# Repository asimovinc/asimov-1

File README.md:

# Asimov v1: Open-Source Humanoid Robot

Asimov is an open-source humanoid robot that you can build, train and customize.

<p align="center">
  <a href="https://asimov.inc">Website</a> ·
  <a href="https://manual.asimov.inc">Manual</a> ·
  <a href="https://asimov.inc/diy-kit">DIY Kit</a> ·
  <a href="https://static.asimov.inc/asimov/v1/asimov-v1-20260420.html">3D Model</a> ·
  <a href="https://discord.gg/HzDfGN7kUw">Discord</a> ·
  <a href="https://x.com/asimovinc">X</a> ·
  <a href="https://forum.menlo.ai">Forum</a>
</p>

Asimov v1 is a 1.2 m, 35 kg biped with 25 actuated degrees of freedom. This repository contains the mechanical CAD, electrical CAD, simulation model, and onboard software to build, simulate, and customize Asimov v1.

---

## Specifications

| Spec | Value |
|---|---|
| Height | 1.2 m |
| Weight | 35 kg |
| Degrees of Freedom | 25 actuated + 2 passive |
| Legs | 6 DOF x 2 + toe x 2 |
| Arms | 5 DOF x 2 (shoulder pitch/roll/yaw, elbow, wrist yaw) |
| Torso | 1 DOF waist yaw, 10 W 4 ohm speaker, 6 DOF IMU |
| Head | 2 DOF neck (neck yaw, neck pitch), Quad microphone array, 2MP monocular camera |
| CAN Bus | 5 @ 1Mbps + 1 @ 500kbps |
| Onboard Compute | Raspberry Pi 5 (media + network) + Radxa CM5 (motion control) |
| Structural Materials | 7075 aluminium, MJF PA12 nylon |

| Activity | Load |
|---|---|
| Squat | 5 kg |
| Bicep curl | 15 kg each arm |
| Lateral raise | 18 kg each arm |

---

## Build your own Asimov

> [!TIP]
> **Option 1: DIY Kit:** Everything you need to build Asimov v1, unassembled. $499 deposit to reserve. $15,000 target price. Ships summer 2026. [Pre-order →](https://asimov.inc/diy-kit)

> [!NOTE]
> **Option 2: Self-source:** Pull the [BOM](https://manual.asimov.inc/v1/bom) and fabricate everything yourself. [Assembly Manual →](https://manual.asimov.inc)

### DIY Kit

| Category | Included | Not Included |
|---|---|---|
| Hardware | All BOM components (unassembled), power supply & cabling, spare parts | Tools, hands |
| Compute | RPi edge board, motion control board, network board, power distribution board | 4G/5G modules |
| Sensors | Monocular camera, IMUs, mic, speaker, motor joint states | Lidar, 360 cam |
| Safety | Wireless E-Stop, safety guidelines | Battery |
| Docs | Quick start guide, manual, DIY build videos | — |

**[Pre-order the Asimov v1 DIY Kit →](https://asimov.inc/diy-kit)**

### Self-source

Start with the repo-local [fabrication manifest](mechanical/FABRICATION_MANIFEST.csv) for the CAD-derived part inventory, then cross-reference the [BOM](https://manual.asimov.inc/v1/bom) and assembly manual for procurement details, sourcing, and fabrication notes.

**[Assembly Manual →](https://manual.asimov.inc)**

---

## Fabrication manifest

The CAD-derived fabrication manifest can be checked locally:

```bash
python3 scripts/generate_fabrication_manifest.py --check
```

---

## Roadmap

| Status | Item |
|---|---|
| ✅ | Mechanical CAD — 7 subassemblies |
| ✅ | MuJoCo simulation model |
| ✅ | Electrical wiring harness |
| ✅ | Electrical schematics & PCB files |
| 🔜 | Asimov API |
| 🔜 | Locomotion policy |
| 🔜 | Mobile app |

---

## Work with us

- **Build questions?**: Ask in the [forum](https://forum.menlo.ai) or open a [GitHub Issue](https://github.com/asimovinc/asimov-v1/issues) for bugs and contributions.
- **Deploying Asimov?**: [Talk to us →](mailto:bd@menlo.ai)
- **Supply chain partner?**: If you manufacture actuators, structural components, or electronics and want to be part of the Asimov supply chain, reach out.
[bd@menlo.ai](mailto:bd@menlo.ai)

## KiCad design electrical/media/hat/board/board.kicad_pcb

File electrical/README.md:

## Motion Control Board

The Motion Control Board (MCB) is a carrier board designed for the Radxa CM5, providing comprehensive connectivity for robotic applications.

- The board serves as a carrier board for the Radxa CM5.
- Power is supplied via a 5V input through an XT30 connector.
- A UART TTL debug port is available for serial debugging purposes.
- The LSM6DSV IMU is located at the bottom of the board, with an I2C connector available if an external IMU is required.
- All signal connections use JST-GH connectors
- LCSC component IDs are attached in the KiCad source files for direct JLCPCB fabrication and assembly.

### Communication Ports

| Port Type | Quantity | Details |
|-----------|----------|---------|
| CAN (Native) | 3 | Direct CAN interfaces |
| CAN (SPI-CAN) | 3 | CAN via SPI bridge |
| USB 2.0 | 3 | USB interfaces |
| Ethernet | 1 | 1Gbps |
| RS485 | 2 | Serial communication |
| I2C | 1 | I2C interface |

### Port Mapping

| Port ID | Purpose |
|---------|---------|
| C0 | Left leg bus |
| C1 | Right leg bus |
| C2 | Right arm bus |
| C3 | Left arm bus |
| C4 | Waist-neck bus |
| C5 | BMS bus |

> The waist-neck bus requires a different cabling setup for this revision of the MCB: Waist -> Neck yaw -> Neck pitch -> MCB port C4

## Wiring

 was utilised for representing the wiring harness of the robot. 

Please refer to WireViz documentation for available visualisation options.
### Cable Naming Convention

```
W-<ID>-<TYPE>
ID = unique ID
TYPE = Power (PWR) or Signal (SIG) cable bundle
```

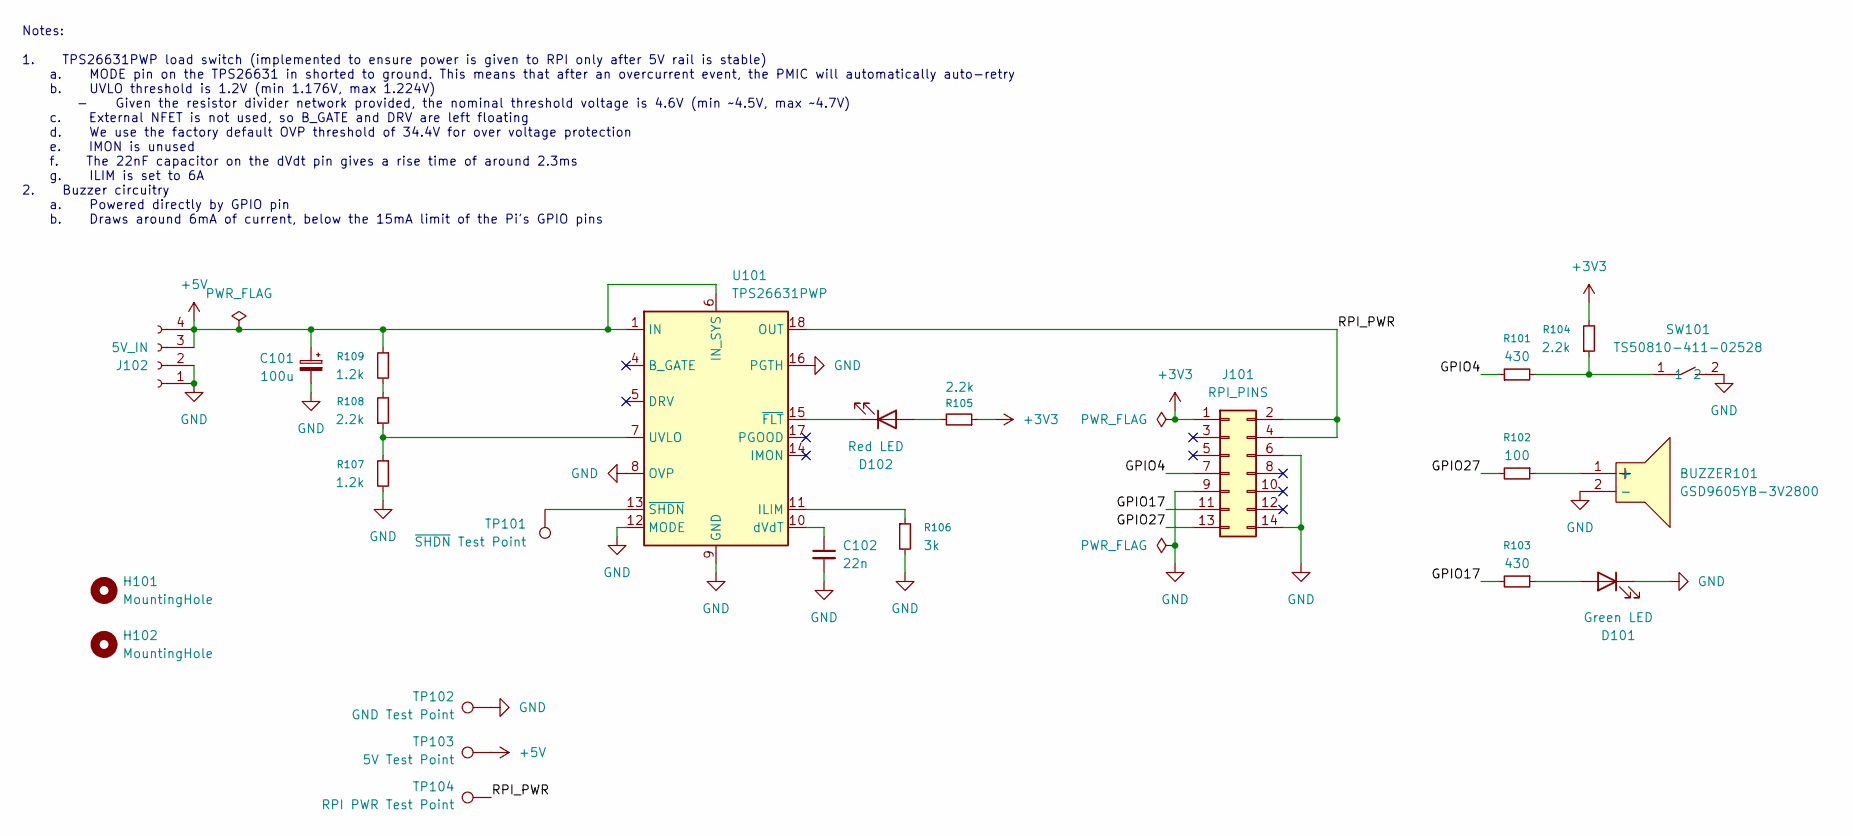
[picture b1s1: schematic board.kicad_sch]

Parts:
BUZZER101: GSD9605YB-3V2800; BUZ-SMD_GSD9605YB-3V2800; MPN GSD9605YB-3V2800; LCSC Part C255327
C101: 100u; CP_EIA-7343-31_Kemet-D; LCSC C600555
C102: 22n; C_0402_1005Metric; LCSC C1532
D101: Green LED; LED_0603_1608Metric; LCSC C965804
D102: Red LED; LED_0603_1608Metric; LCSC C2286
H101, H102: MountingHole; MountingHole_2.5mm
J101: RPI_PINS; PinSocket_2x07_P2.54mm_Vertical; LCSC C5116484
J102: 5V_IN; JST_XH_B4B-XH-A_1x04_P2.50mm_Vertical; LCSC C144395
R101, R103: 430; R_0402_1005Metric; LCSC C137868
R102: 100; R_0402_1005Metric; LCSC C25076
R104, R105, R108: 2.2k; R_0402_1005Metric; LCSC C25879
R106: 3k; R_0603_1608Metric; LCSC C4211
R107, R109: 1.2k; R_0402_1005Metric; LCSC C2909307
SW101: TS50810-411-02528; SW-SMD_L6.2-W3.7-LS8.0; MPN TS50810-411-02528; LCSC Part C42400876
TP101: ~{SHDN} Test Point; TestPoint_Keystone_5015_Micro_Mini; LCSC C5199798
TP102: GND Test Point; TestPoint_Keystone_5015_Micro_Mini; LCSC C5199798
TP103: 5V Test Point; TestPoint_Keystone_5015_Micro_Mini; LCSC C5199798
TP104: RPI PWR Test Point; TestPoint_Keystone_5015_Micro_Mini; LCSC C5199798
U101: TPS26631PWP; HTSSOP-20-1EP_4.4x6.5mm_P0.65mm_EP3.4x6.5mm_Mask2.96x2.96mm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; LCSC C2866319

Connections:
+3V3: J101.1, R104.2, R105.1
+5V: C101.1, J102.3, J102.4, R109.1, TP103.1 (1_1), U101.1 (IN), U101.2 (IN), U101.3 (IN), U101.6 (IN_SYS)
/GPIO4: J101.7, R101.1
/GPIO17: J101.11, R103.2
/GPIO27: J101.13, R102.2
/RPI_PWR: J101.2, J101.4, TP104.1 (1_1), U101.18 (OUT), U101.19 (OUT), U101.20 (OUT)
GND: BUZZER101.2 (-), C101.2, C102.2, D101.1 (K), J101.6, J101.9, J101.14, J102.1, J102.2, R106.2, R107.2, SW101.2, TP102.1 (1_1), U101.8 (OVP), U101.9 (GND), U101.12 (MODE), U101.16 (PGTH), U101.21 (GND)
unnamed: BUZZER101.1 (+), R102.1
unnamed: D101.2 (A), R103.1
unnamed: D102.2 (A), R105.2
unnamed: D102.1 (K), U101.15 (~FLT)
unnamed: R101.2, R104.1, SW101.1
unnamed: R108.2, R109.2
unnamed: R106.1, U101.11 (ILIM)
unnamed: R107.1, R108.1, U101.7 (UVLO)
unnamed: C102.1, U101.10 (dVdT)
unnamed: TP101.1 (1_1), U101.13 (~SHDN)

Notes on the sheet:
Notes: 1. TPS26631PWP load switch (implemented to ensure power is given to RPI only after 5V rail is stable) a. MODE pin on the TPS26631 in shorted to ground. This means that after an overcurrent event, the PMIC will automatically auto-retry b. UVLO threshold is 1.2V (min 1.176V, max 1.224V) - Give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

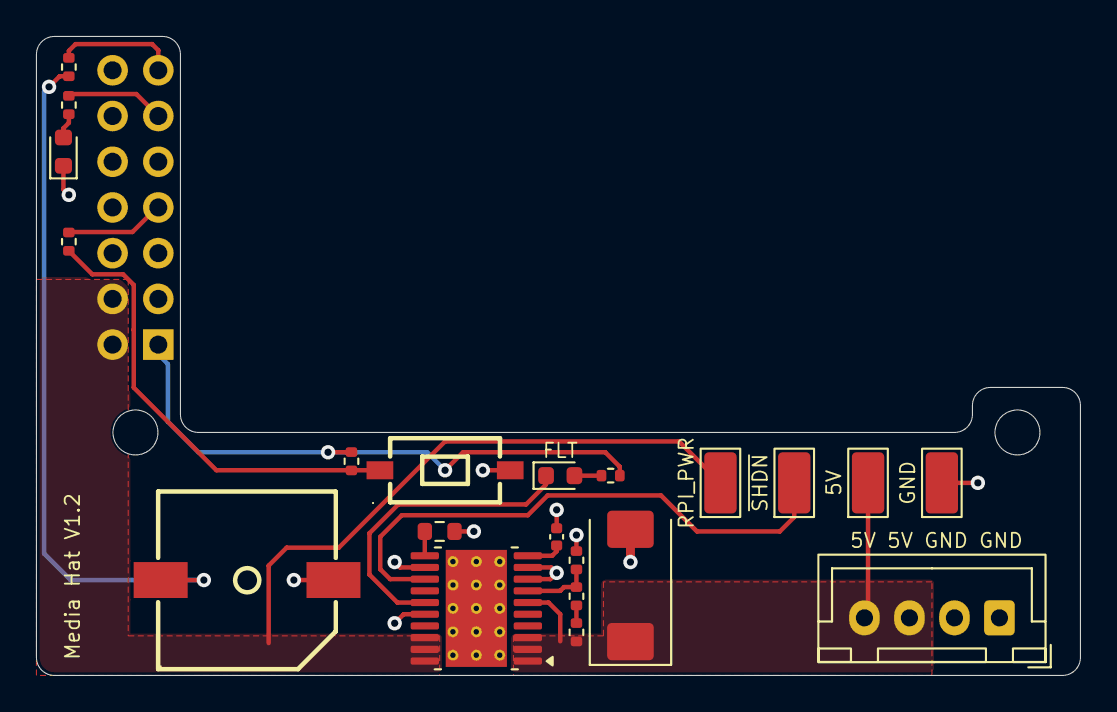
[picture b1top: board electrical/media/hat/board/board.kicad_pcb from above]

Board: 2 copper layers, 58.0 x 35.5 mm, 24 parts (1 on the bottom side), 17 nets.

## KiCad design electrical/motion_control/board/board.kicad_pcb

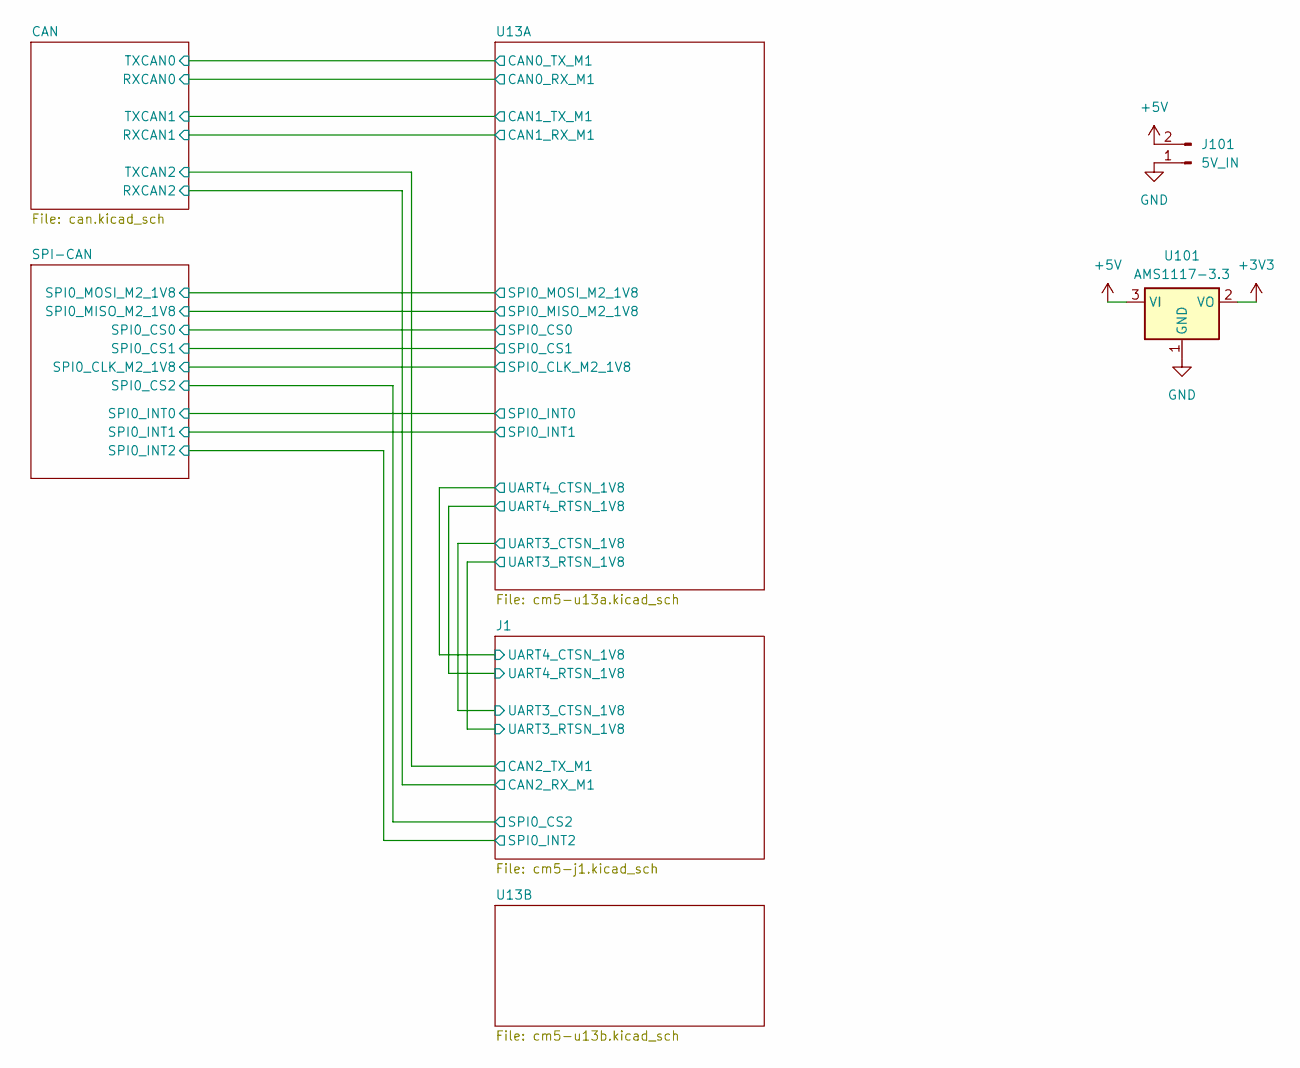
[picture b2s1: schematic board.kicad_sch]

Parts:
J101: 5V_IN; AMASS_XT30UPB-F_1x02_P5.0mm_Vertical; LCSC C108769
U101: AMS1117-3.3; SOT-223-3_TabPin2; LCSC C6186

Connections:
+3V3: U101.2 (VO); also elsewhere on the board
+5V: J101.2, U101.3 (VI); also elsewhere on the board
GND: J101.1, U101.1 (GND); also elsewhere on the board

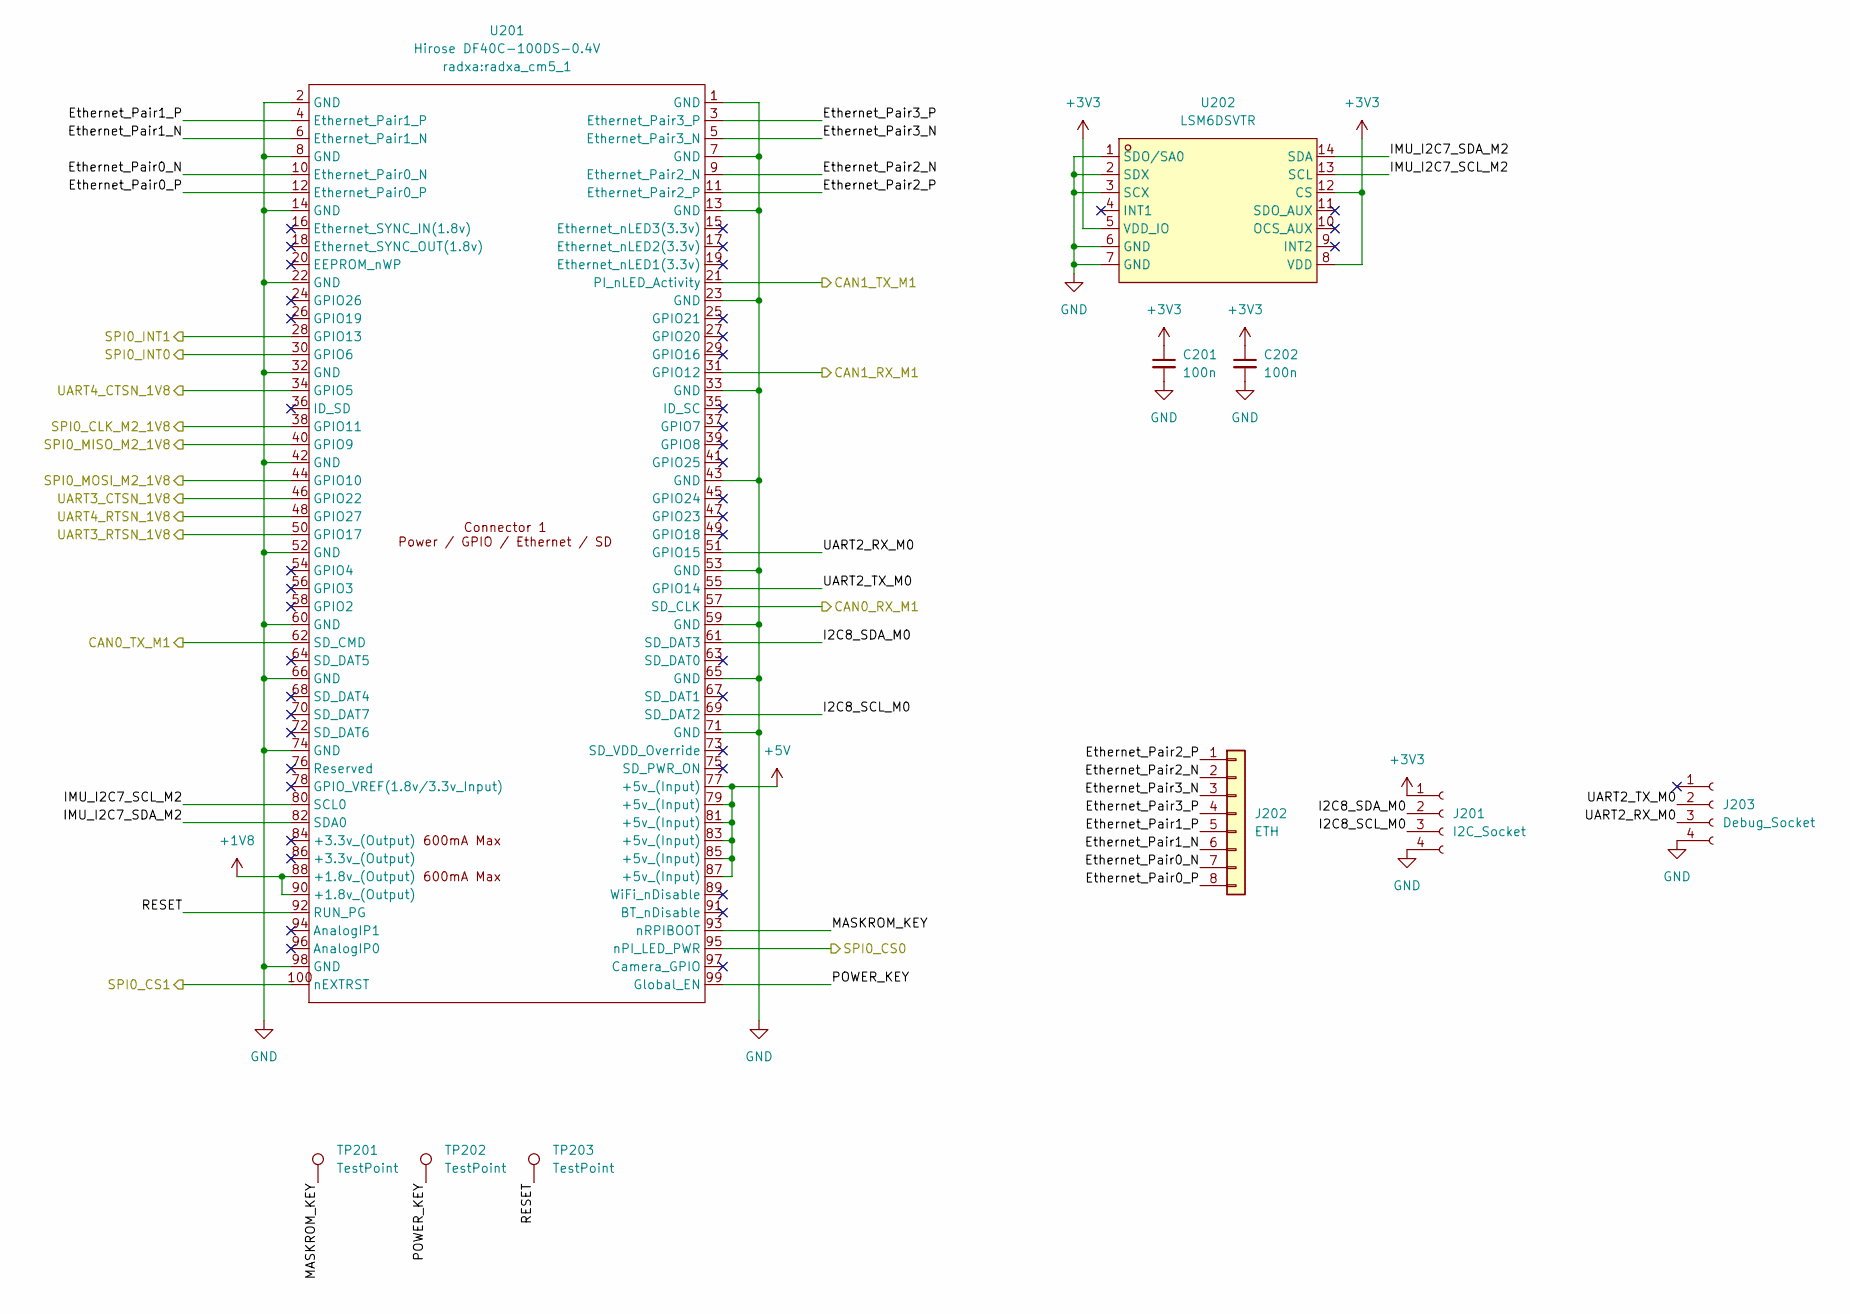
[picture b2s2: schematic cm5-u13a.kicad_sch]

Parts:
C201, C202: 100n; C_0402_1005Metric; LCSC C77020
J201: I2C_Socket; JST_GH_SM04B-GHS-TB_1x04-1MP_P1.25mm_Horizontal; LCSC C51940118
J202: ETH; JST_GH_BM08B-GHS-TBT_1x08-1MP_P1.25mm_Vertical; LCSC C133062
J203: Debug_Socket; JST_GH_SM04B-GHS-TB_1x04-1MP_P1.25mm_Horizontal; LCSC C51940118
TP201, TP202, TP203: TestPoint; TestPoint_Pad_D1.0mm
U201: Hirose DF40C-100DS-0.4V; radxa_cm5_1; LCSC C597931
U202: LSM6DSVTR; LGA-14_L3.0-W2.5-P0.50-TL; LCSC Part C5267399

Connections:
+1V8: U201.88 (+1.8v_(Output)), U201.90 (+1.8v_(Output)); also elsewhere on the board
+3V3: C201.1, C202.1, J201.1, U202.5 (VDD_IO), U202.8 (VDD), U202.12 (CS); also elsewhere on the board
+5V: U201.77 (+5v_(Input)), U201.79 (+5v_(Input)), U201.81 (+5v_(Input)), U201.83 (+5v_(Input)), U201.85 (+5v_(Input)), U201.87 (+5v_(Input)); also elsewhere on the board
/CAN/RXCAN0: U201.57 (SD_CLK); also elsewhere on the board
/CAN/RXCAN1: U201.31 (GPIO12); also elsewhere on the board
/CAN/TXCAN0: U201.62 (SD_CMD); also elsewhere on the board
/CAN/TXCAN1: U201.21 (PI_nLED_Activity); also elsewhere on the board
/J1/UART3_CTSN_1V8: U201.46 (GPIO22); also elsewhere on the board
/J1/UART3_RTSN_1V8: U201.50 (GPIO17); also elsewhere on the board
/J1/UART4_CTSN_1V8: U201.34 (GPIO5); also elsewhere on the board
/J1/UART4_RTSN_1V8: U201.48 (GPIO27); also elsewhere on the board
/SPI-CAN/SPI0_CLK_M2_1V8: U201.38 (GPIO11); also elsewhere on the board
/SPI-CAN/SPI0_CS0: U201.95 (nPI_LED_PWR); also elsewhere on the board
/SPI-CAN/SPI0_CS1: U201.100 (nEXTRST); also elsewhere on the board
/SPI-CAN/SPI0_INT0: U201.30 (GPIO6); also elsewhere on the board
/SPI-CAN/SPI0_INT1: U201.28 (GPIO13); also elsewhere on the board
/SPI-CAN/SPI0_MISO_M2_1V8: U201.40 (GPIO9); also elsewhere on the board
/SPI-CAN/SPI0_MOSI_M2_1V8: U201.44 (GPIO10); also elsewhere on the board
/U13A/Ethernet_Pair0_N: J202.7, U201.10 (Ethernet_Pair0_N)
/U13A/Ethernet_Pair0_P: J202.8, U201.12 (Ethernet_Pair0_P)
/U13A/Ethernet_Pair1_N: J202.6, U201.6 (Ethernet_Pair1_N)
/U13A/Ethernet_Pair1_P: J202.5, U201.4 (Ethernet_Pair1_P)
/U13A/Ethernet_Pair2_N: J202.2, U201.9 (Ethernet_Pair2_N)
/U13A/Ethernet_Pair2_P: J202.1, U201.11 (Ethernet_Pair2_P)
/U13A/Ethernet_Pair3_N: J202.3, U201.5 (Ethernet_Pair3_N)
/U13A/Ethernet_Pair3_P: J202.4, U201.3 (Ethernet_Pair3_P)
/U13A/I2C8_SCL_M0: J201.3, U201.69 (SD_DAT2)
/U13A/I2C8_SDA_M0: J201.2, U201.61 (SD_DAT3)
/U13A/IMU_I2C7_SCL_M2: U201.80 (SCL0), U202.13 (SCL)
/U13A/IMU_I2C7_SDA_M2: U201.82 (SDA0), U202.14 (SDA)
/U13A/MASKROM_KEY: TP201.1, U201.93 (nRPIBOOT)
/U13A/POWER_KEY: TP202.1, U201.99 (Global_EN)
/U13A/RESET: TP203.1, U201.92 (RUN_PG)
/U13A/UART2_RX_M0: J203.3, U201.51 (GPIO15)
/U13A/UART2_TX_M0: J203.2, U201.55 (GPIO14)
GND: C201.2, C202.2, J201.4, J203.4, U201.1 (GND), U201.2 (GND), U201.7 (GND), U201.8 (GND), U201.13 (GND), U201.14 (GND), U201.22 (GND), U201.23 (GND), U201.32 (GND), U201.33 (GND), U201.42 (GND), U201.43 (GND), U201.52 (GND), U201.53 (GND), U201.59 (GND), U201.60 (GND), U201.65 (GND), U201.66 (GND), U201.71 (GND), U201.74 (GND), U201.98 (GND), U202.1 (SDO/SA0), U202.2 (SDX), U202.3 (SCX), U202.6 (GND), U202.7 (GND); also elsewhere on the board

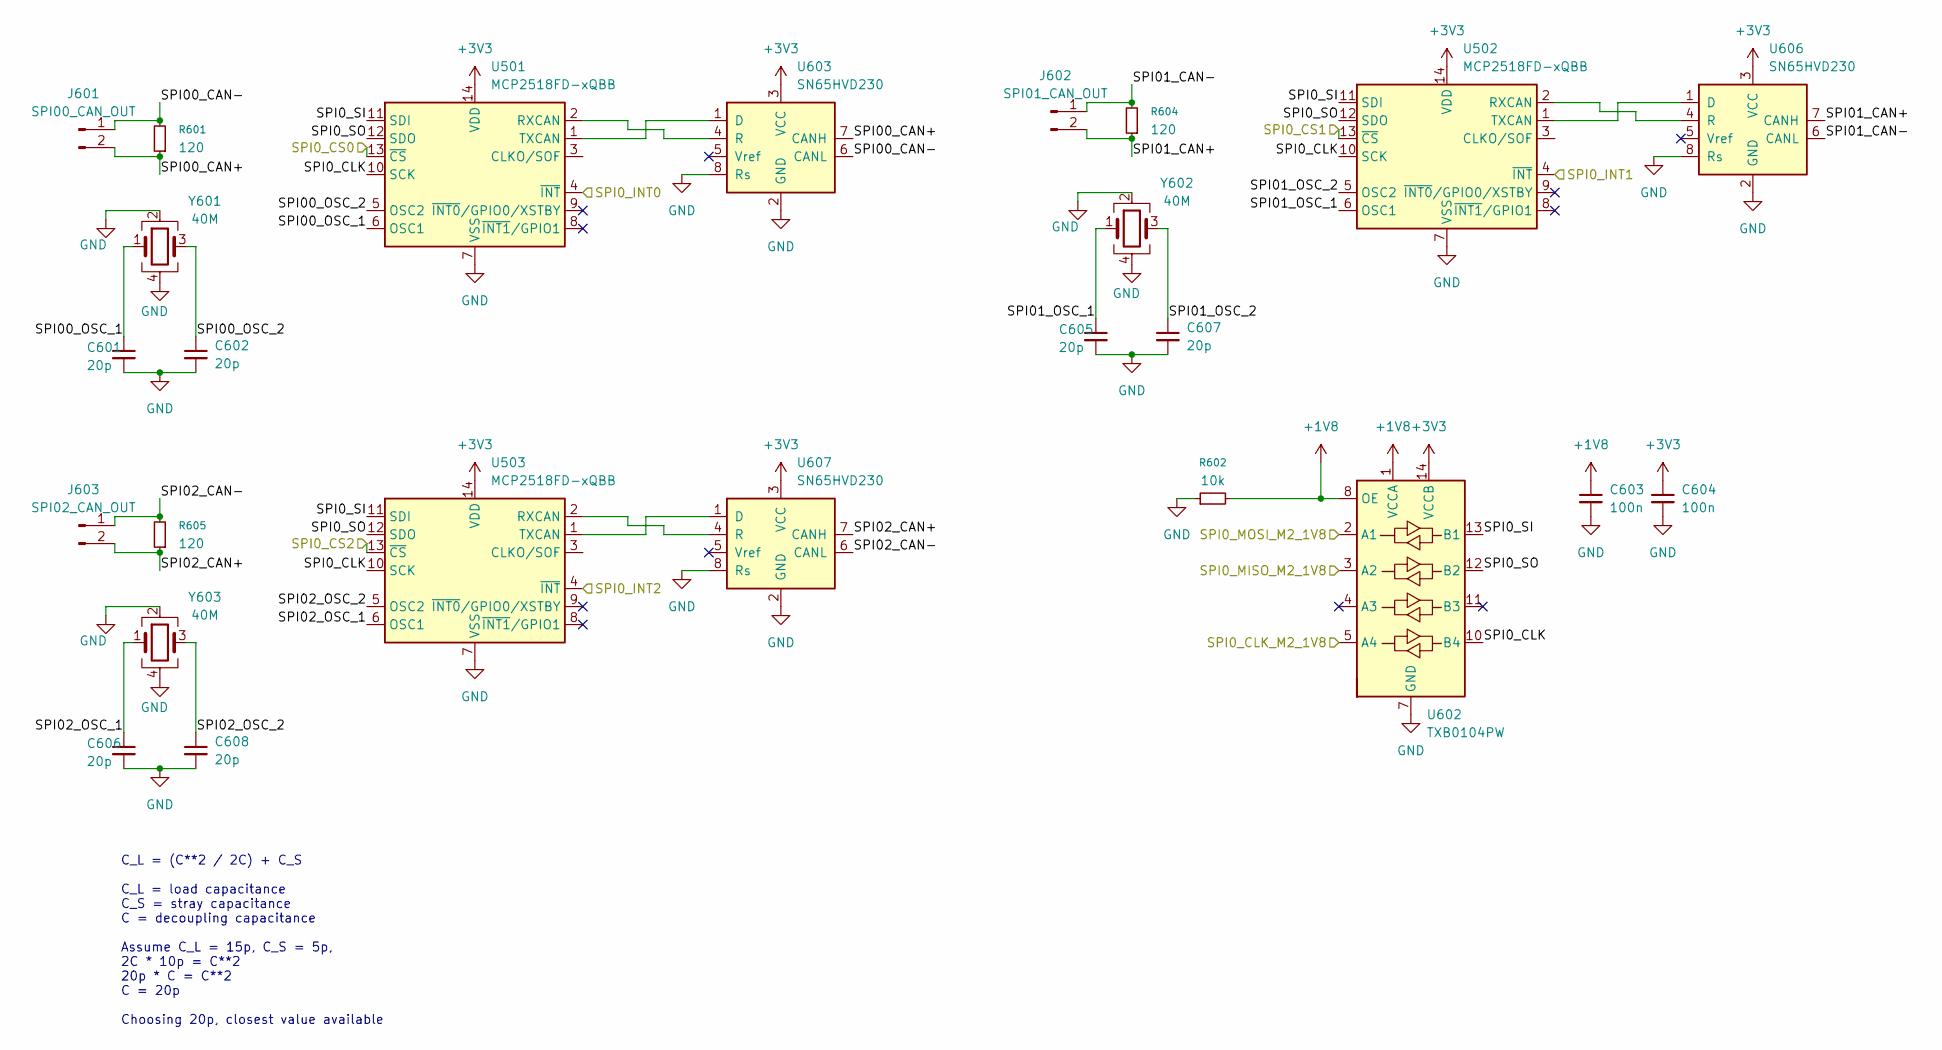
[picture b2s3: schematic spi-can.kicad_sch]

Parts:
C601, C602, C605, C606, C607, C608: 20p; C_0603_1608Metric; LCSC C165732
C603, C604: 100n; C_0402_1005Metric; LCSC C77020
J601: SPI00_CAN_OUT; JST_GH_SM02B-GHS-TB_1x02-1MP_P1.25mm_Horizontal; LCSC C189893
J602: SPI01_CAN_OUT; JST_GH_SM02B-GHS-TB_1x02-1MP_P1.25mm_Horizontal; LCSC C189893
J603: SPI02_CAN_OUT; JST_GH_SM02B-GHS-TB_1x02-1MP_P1.25mm_Horizontal; LCSC C189893
R601, R604, R605: 120; R_0402_1005Metric; LCSC C114758
R602: 10k; R_0402_1005Metric; LCSC C190095
U501, U502, U503: MCP2518FD-xQBB; SOIC-14_3.9x8.7mm_P1.27mm; LCSC C626758
U602: TXB0104PW; TSSOP-14_4.4x5mm_P0.65mm; LCSC C60708
U603, U606, U607: SN65HVD230; SOIC-8_3.9x4.9mm_P1.27mm; LCSC C12084
Y601, Y602, Y603: 40M; Crystal_SMD_3225-4Pin_3.2x2.5mm; LCSC C5444549

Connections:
+1V8: C603.1, R602.2, U602.1 (VCCA), U602.8 (OE); also elsewhere on the board
+3V3: C604.1, U501.14 (VDD), U502.14 (VDD), U503.14 (VDD), U602.14 (VCCB), U603.3 (VCC), U606.3 (VCC), U607.3 (VCC); also elsewhere on the board
/J1/SPI0_CS2: U503.13 (~CS); also elsewhere on the board
/J1/SPI0_INT2: U503.4 (~INT); also elsewhere on the board
/SPI-CAN/SPI00_CAN+: J601.2, R601.1, U603.7 (CANH)
/SPI-CAN/SPI00_CAN-: J601.1, R601.2, U603.6 (CANL)
/SPI-CAN/SPI0_CLK: U501.10 (SCK), U502.10 (SCK), U503.10 (SCK), U602.10 (B4)
/SPI-CAN/SPI0_CLK_M2_1V8: U602.5 (A4); also elsewhere on the board
/SPI-CAN/SPI0_CS0: U501.13 (~CS); also elsewhere on the board
/SPI-CAN/SPI0_CS1: U502.13 (~CS); also elsewhere on the board
/SPI-CAN/SPI0_INT0: U501.4 (~INT); also elsewhere on the board
/SPI-CAN/SPI0_INT1: U502.4 (~INT); also elsewhere on the board
/SPI-CAN/SPI0_MISO_M2_1V8: U602.3 (A2); also elsewhere on the board
/SPI-CAN/SPI0_MOSI_M2_1V8: U602.2 (A1); also elsewhere on the board
/SPI-CAN/SPI00_OSC_1: C601.1, U501.6 (OSC1), Y601.1
/SPI-CAN/SPI00_OSC_2: C602.1, U501.5 (OSC2), Y601.3
/SPI-CAN/SPI0_SI: U501.11 (SDI), U502.11 (SDI), U503.11 (SDI), U602.13 (B1)
/SPI-CAN/SPI0_SO: U501.12 (SDO), U502.12 (SDO), U503.12 (SDO), U602.12 (B2)
/SPI-CAN/SPI01_CAN+: J602.2, R604.1, U606.7 (CANH)
/SPI-CAN/SPI01_CAN-: J602.1, R604.2, U606.6 (CANL)
/SPI-CAN/SPI01_OSC_1: C605.1, U502.6 (OSC1), Y602.1
/SPI-CAN/SPI01_OSC_2: C607.1, U502.5 (OSC2), Y602.3
/SPI-CAN/SPI02_CAN+: J603.2, R605.1, U607.7 (CANH)
/SPI-CAN/SPI02_CAN-: J603.1, R605.2, U607.6 (CANL)
/SPI-CAN/SPI02_OSC_1: C606.1, U503.6 (OSC1), Y603.1
/SPI-CAN/SPI02_OSC_2: C608.1, U503.5 (OSC2), Y603.3
GND: C601.2, C602.2, C603.2, C604.2, C605.2, C606.2, C607.2, C608.2, R602.1, U501.7 (VSS), U501.15 (VSS), U502.7 (VSS), U502.15 (VSS), U503.7 (VSS), U503.15 (VSS), U602.7 (GND), U603.2 (GND), U603.8 (Rs), U606.2 (GND), U606.8 (Rs), U607.2 (GND), U607.8 (Rs), Y601.2, Y601.4, Y602.2, Y602.4, Y603.2, Y603.4; also elsewhere on the board
unnamed: U501.2 (RXCAN), U603.4 (R)
unnamed: U501.1 (TXCAN), U603.1 (D)
unnamed: U502.2 (RXCAN), U606.4 (R)
unnamed: U502.1 (TXCAN), U606.1 (D)
unnamed: U503.2 (RXCAN), U607.4 (R)
unnamed: U503.1 (TXCAN), U607.1 (D)

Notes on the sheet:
C_L = (C**2 / 2C) + C_S C_L = load capacitance C_S = stray capacitance C = decoupling capacitance Assume C_L = 15p, C_S = 5p, 2C * 10p = C**2 20p * C = C**2 C = 20p Choosing 20p, closest value available

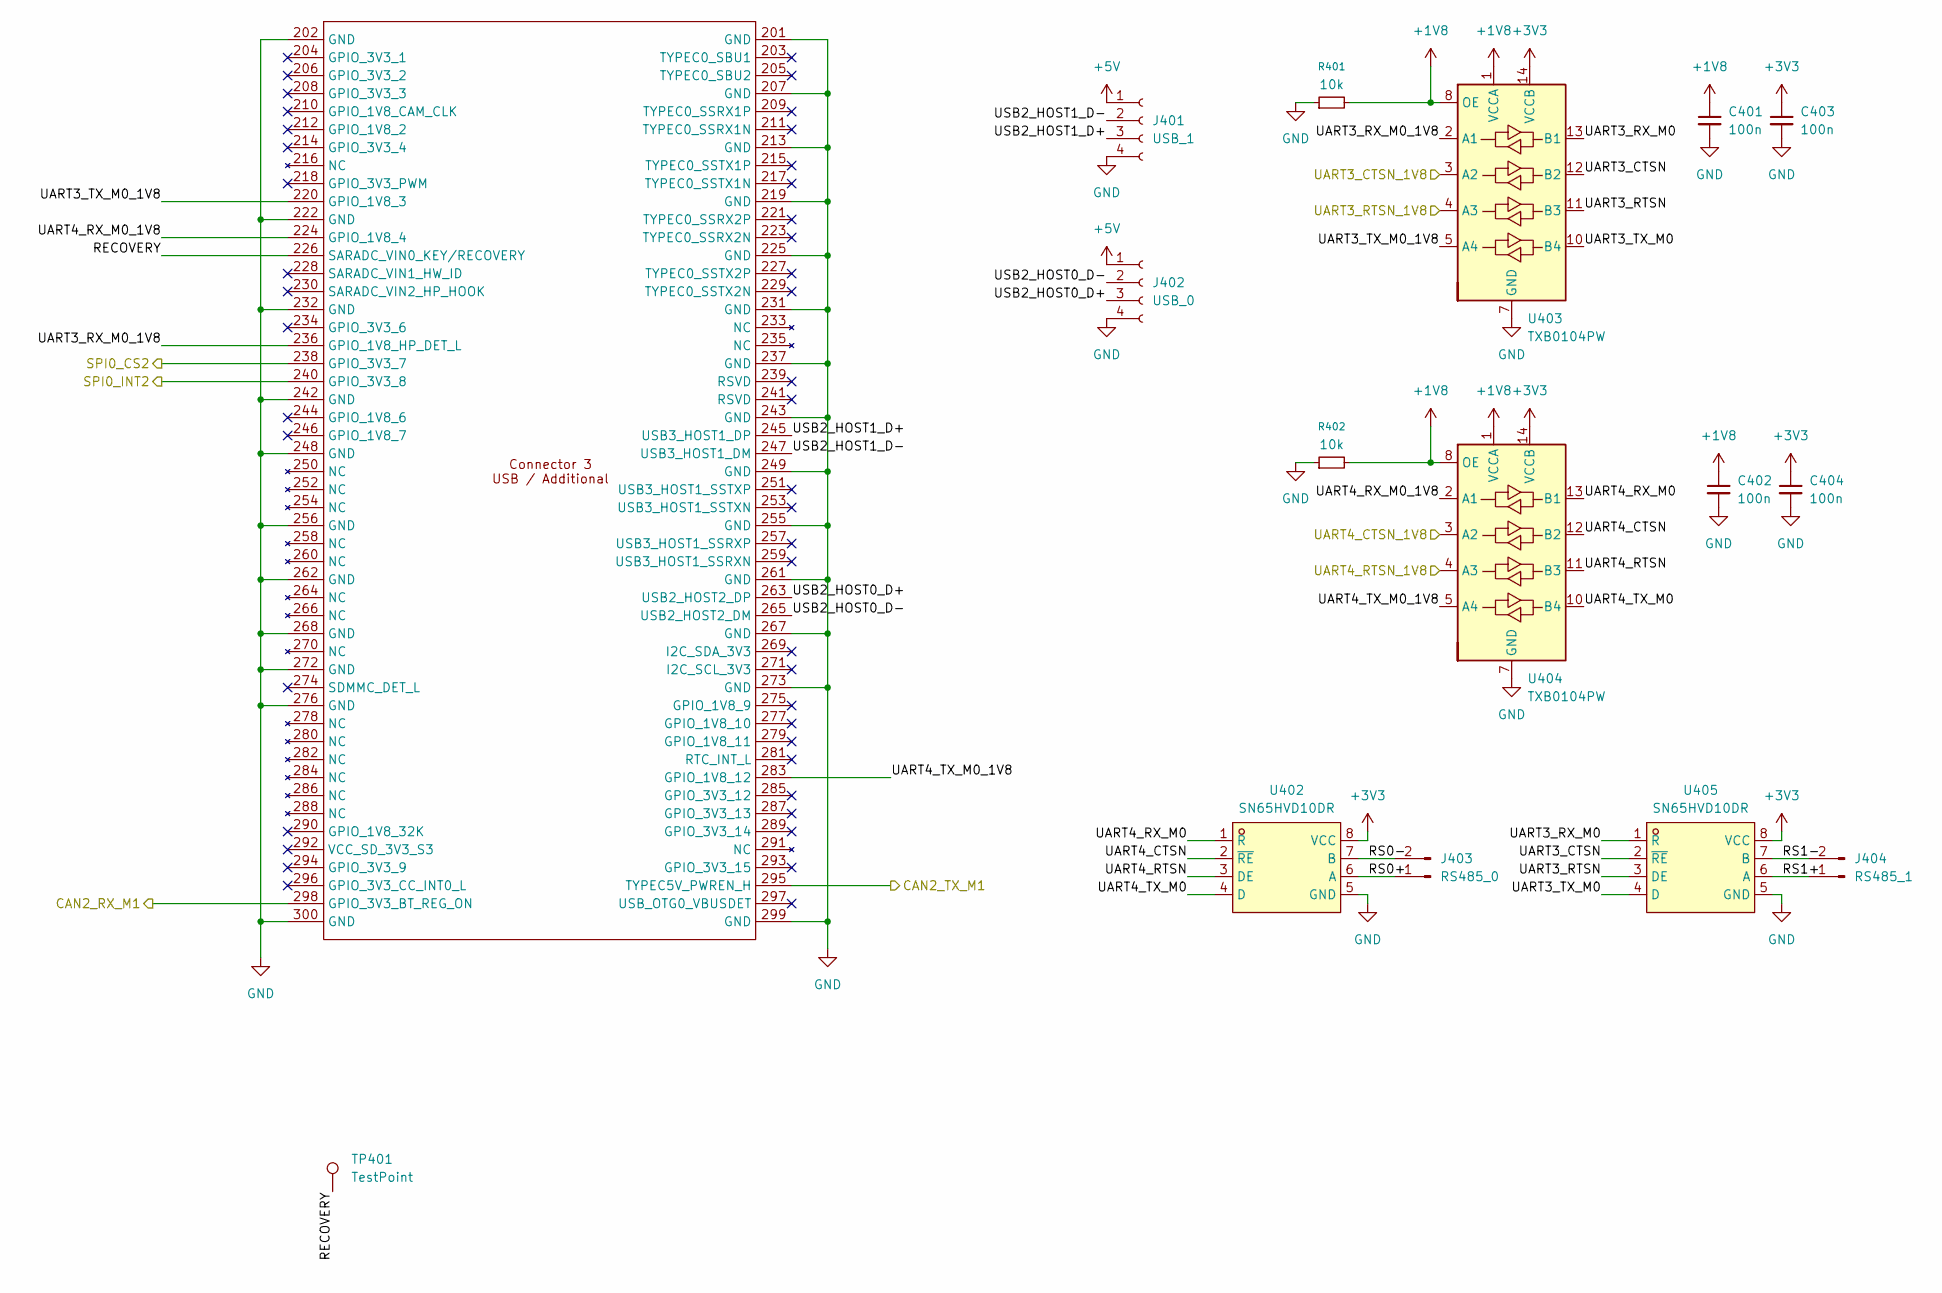
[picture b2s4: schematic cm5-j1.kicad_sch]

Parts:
C401, C402, C403, C404: 100n; C_0402_1005Metric; LCSC C77020
J401: USB_1; JST_GH_SM04B-GHS-TB_1x04-1MP_P1.25mm_Horizontal; LCSC C51940118
J402: USB_0; JST_GH_SM04B-GHS-TB_1x04-1MP_P1.25mm_Horizontal; LCSC C51940118
J403: RS485_0; JST_GH_SM02B-GHS-TB_1x02-1MP_P1.25mm_Horizontal; LCSC C189893
J404: RS485_1; JST_GH_SM02B-GHS-TB_1x02-1MP_P1.25mm_Horizontal; LCSC C189893
R401, R402: 10k; R_0402_1005Metric; LCSC C190095
TP401: TestPoint; TestPoint_Pad_D1.0mm
U401: Hirose DF40C-100DS-0.4V; radxa_cm5_3; LCSC C597931
U402, U405: SN65HVD10DR; SOIC-8_L4.9-W3.9-P1.27-LS6.0-BL; LCSC Part C148982
U403, U404: TXB0104PW; TSSOP-14_4.4x5mm_P0.65mm; LCSC C60708

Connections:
+1V8: C401.1, C402.1, R401.2, R402.2, U403.1 (VCCA), U403.8 (OE), U404.1 (VCCA), U404.8 (OE); also elsewhere on the board
+3V3: C403.1, C404.1, U402.8 (VCC), U403.14 (VCCB), U404.14 (VCCB), U405.8 (VCC); also elsewhere on the board
+5V: J401.1, J402.1; also elsewhere on the board
/CAN/RXCAN2: U401.298 (GPIO_3V3_BT_REG_ON); also elsewhere on the board
/CAN/TXCAN2: U401.295 (TYPEC5V_PWREN_H); also elsewhere on the board
/J1/RECOVERY: TP401.1, U401.226 (SARADC_VIN0_KEY/RECOVERY)
/J1/RS0+: J403.1, U402.6 (A)
/J1/RS0-: J403.2, U402.7 (B)
/J1/RS1+: J404.1, U405.6 (A)
/J1/RS1-: J404.2, U405.7 (B)
/J1/SPI0_CS2: U401.238 (GPIO_3V3_7); also elsewhere on the board
/J1/SPI0_INT2: U401.240 (GPIO_3V3_8); also elsewhere on the board
/J1/UART3_CTSN: U403.12 (B2), U405.2 (~RE)
/J1/UART3_CTSN_1V8: U403.3 (A2); also elsewhere on the board
/J1/UART3_RTSN: U403.11 (B3), U405.3 (DE)
/J1/UART3_RTSN_1V8: U403.4 (A3); also elsewhere on the board
/J1/UART3_RX_M0: U403.13 (B1), U405.1 (R)
/J1/UART3_RX_M0_1V8: U401.236 (GPIO_1V8_HP_DET_L), U403.2 (A1)
/J1/UART3_TX_M0: U403.10 (B4), U405.4 (D)
/J1/UART3_TX_M0_1V8: U401.220 (GPIO_1V8_3), U403.5 (A4)
/J1/UART4_CTSN: U402.2 (~RE), U404.12 (B2)
/J1/UART4_CTSN_1V8: U404.3 (A2); also elsewhere on the board
/J1/UART4_RTSN: U402.3 (DE), U404.11 (B3)
/J1/UART4_RTSN_1V8: U404.4 (A3); also elsewhere on the board
/J1/UART4_RX_M0: U402.1 (R), U404.13 (B1)
/J1/UART4_RX_M0_1V8: U401.224 (GPIO_1V8_4), U404.2 (A1)
/J1/UART4_TX_M0: U402.4 (D), U404.10 (B4)
/J1/UART4_TX_M0_1V8: U401.283 (GPIO_1V8_12), U404.5 (A4)
/J1/USB2_HOST0_D+: J402.3, U401.263 (USB2_HOST2_DP)
/J1/USB2_HOST0_D-: J402.2, U401.265 (USB2_HOST2_DM)
/J1/USB2_HOST1_D+: J401.3, U401.245 (USB3_HOST1_DP)
/J1/USB2_HOST1_D-: J401.2, U401.247 (USB3_HOST1_DM)
GND: C401.2, C402.2, C403.2, C404.2, J401.4, J402.4, R401.1, R402.1, U401.201 (GND), U401.202 (GND), U401.207 (GND), U401.213 (GND), U401.219 (GND), U401.222 (GND), U401.225 (GND), U401.231 (GND), U401.232 (GND), U401.237 (GND), U401.242 (GND), U401.243 (GND), U401.248 (GND), U401.249 (GND), U401.255 (GND), U401.256 (GND), U401.261 (GND), U401.262 (GND), U401.267 (GND), U401.268 (GND), U401.272 (GND), U401.273 (GND), U401.276 (GND), U401.299 (GND), U401.300 (GND), U402.5 (GND), U403.7 (GND), U404.7 (GND), U405.5 (GND); also elsewhere on the board

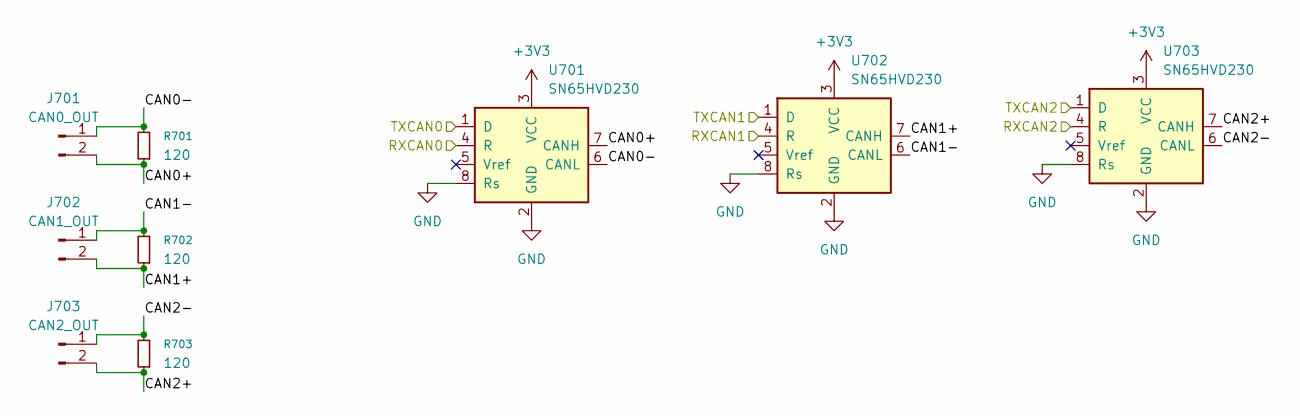
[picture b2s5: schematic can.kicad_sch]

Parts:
J701: CAN0_OUT; JST_GH_SM02B-GHS-TB_1x02-1MP_P1.25mm_Horizontal; LCSC C189893
J702: CAN1_OUT; JST_GH_SM02B-GHS-TB_1x02-1MP_P1.25mm_Horizontal; LCSC C189893
J703: CAN2_OUT; JST_GH_SM02B-GHS-TB_1x02-1MP_P1.25mm_Horizontal; LCSC C189893
R701, R702, R703: 120; R_0402_1005Metric; LCSC C114758
U701, U702, U703: SN65HVD230; SOIC-8_3.9x4.9mm_P1.27mm; LCSC C12084

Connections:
+3V3: U701.3 (VCC), U702.3 (VCC), U703.3 (VCC); also elsewhere on the board
/CAN/CAN0+: J701.2, R701.1, U701.7 (CANH)
/CAN/CAN0-: J701.1, R701.2, U701.6 (CANL)
/CAN/CAN1+: J702.2, R702.1, U702.7 (CANH)
/CAN/CAN1-: J702.1, R702.2, U702.6 (CANL)
/CAN/CAN2+: J703.2, R703.1, U703.7 (CANH)
/CAN/CAN2-: J703.1, R703.2, U703.6 (CANL)
/CAN/RXCAN0: U701.4 (R); also elsewhere on the board
/CAN/RXCAN1: U702.4 (R); also elsewhere on the board
/CAN/RXCAN2: U703.4 (R); also elsewhere on the board
/CAN/TXCAN0: U701.1 (D); also elsewhere on the board
/CAN/TXCAN1: U702.1 (D); also elsewhere on the board
/CAN/TXCAN2: U703.1 (D); also elsewhere on the board
GND: U701.2 (GND), U701.8 (Rs), U702.2 (GND), U702.8 (Rs), U703.2 (GND), U703.8 (Rs); also elsewhere on the board

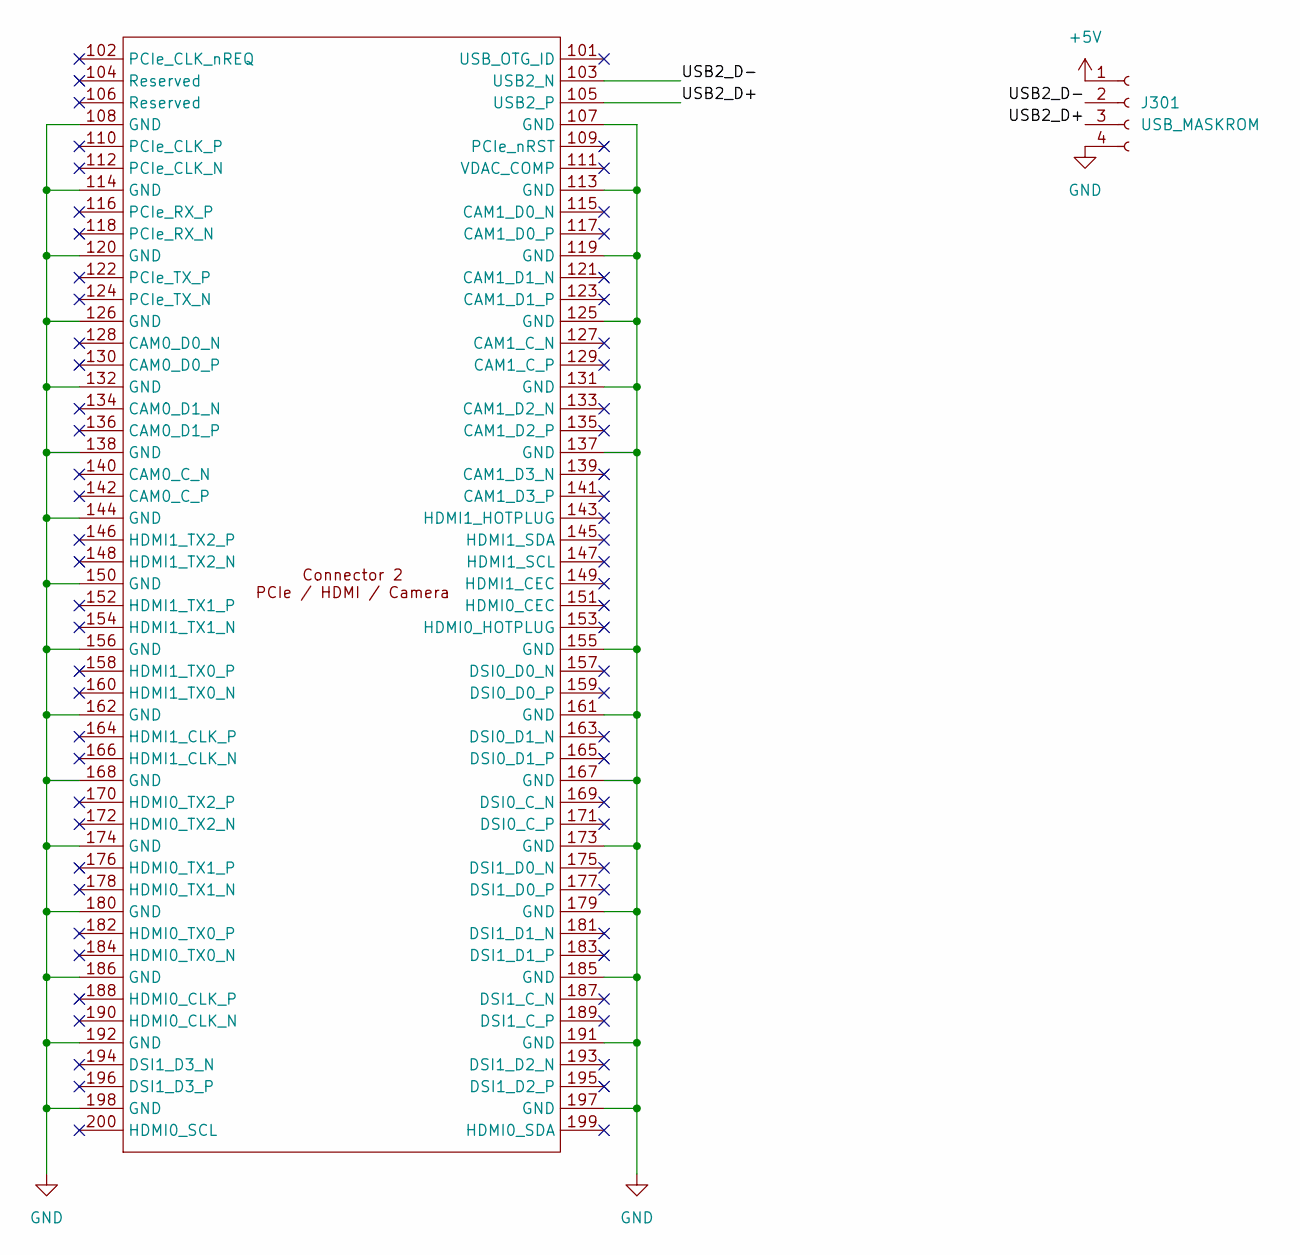
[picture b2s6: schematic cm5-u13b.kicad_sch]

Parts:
J301: USB_MASKROM; JST_GH_SM04B-GHS-TB_1x04-1MP_P1.25mm_Horizontal; LCSC C51940118
U301: Hirose DF40C-100DS-0.4V; radxa_cm5_2; LCSC C597931

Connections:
+5V: J301.1; also elsewhere on the board
/U13B/USB2_D+: J301.3, U301.105 (USB2_P)
/U13B/USB2_D-: J301.2, U301.103 (USB2_N)
GND: J301.4, U301.107 (GND), U301.108 (GND), U301.113 (GND), U301.114 (GND), U301.119 (GND), U301.120 (GND), U301.125 (GND), U301.126 (GND), U301.131 (GND), U301.132 (GND), U301.137 (GND), U301.138 (GND), U301.144 (GND), U301.150 (GND), U301.155 (GND), U301.156 (GND), U301.161 (GND), U301.162 (GND), U301.167 (GND), U301.168 (GND), U301.173 (GND), U301.174 (GND), U301.179 (GND), U301.180 (GND), U301.185 (GND), U301.186 (GND), U301.191 (GND), U301.192 (GND), U301.197 (GND), U301.198 (GND); also elsewhere on the board

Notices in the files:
README.md:
License: CERN-OHL-S-2.0
License: Software
